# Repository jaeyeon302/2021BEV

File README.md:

# 2021BEV 
2021 Bachelor's degree Graduation Project, Battery Electric Vehicle  
Department of Electrical and Conputer Engineering, Seoul National University  

- Advisor : [Professor Seung-ki Sul](http://eepel.snu.ac.kr/wordpress/professor/)

## Demo Video

### [Test driving 1 : Seoul National University Campus Road (youtube video)](https://youtu.be/YFAJCFfAURw)
- Path length : 4.06Km
- Maximum slope : 7%
- Maximum speed : 30.5km/h

### [Test driving 2 : Cooling Performance test (youtube video)](https://youtu.be/0JFbmtatzrk)
- place : Seoul National University Electric Power Research Institute Parking Lot
- settled down at 44 celcius degree
- continuous maximum q-axis current (30A)

## What I made

### Inverter
- 4 layer PCB artwork (1oz 2oz 2oz 1oz) 
- Used IPM([NFAL5065L4B](https://kr.mouser.com/datasheet/2/308/1/NFAL5065L4B_D-2317681.pdf)) as the power IGBT switch
- Electrically isolated control board area from the High Power Area including IPM and DC link

### DSP - controller
- TMS320F2839D Launchpad
- Built the q-axis current regulator(PI controller with feedforward) from the scratch including resgister setting(ePWM, eCAP, GPIO, Clock, Timer)
- Implemented rotor position and speed observer to estimate right position of rotor for DQ transformation and feedforward control

## Future work
- Robust control algorithm to prevent sudden current peak from the disturbance.   
  Since there is no mechanical damper between ground and motor wheel, Bumpy road surface directly affects the controller's performance
- Hall sensor type curernt sensor removal. because the IPM already provides extra ports to measure the phase current using small register.

## Photos
- [Bicycle Photo](https://photos.app.goo.gl/71CFiTBS6PbSPb559)
- [Inverter Photo](https://photos.app.goo.gl/JQpmmjE8fstSpoiK7)

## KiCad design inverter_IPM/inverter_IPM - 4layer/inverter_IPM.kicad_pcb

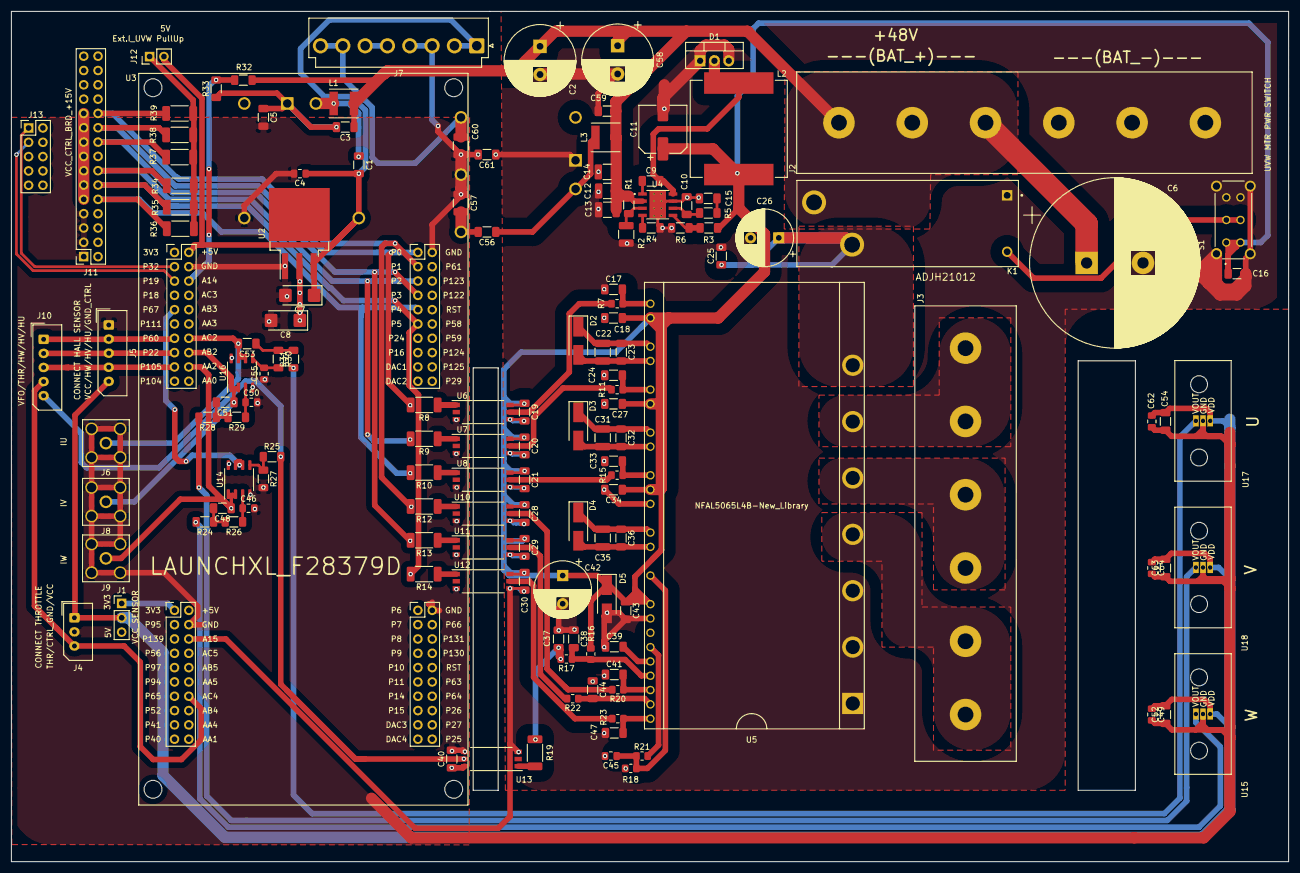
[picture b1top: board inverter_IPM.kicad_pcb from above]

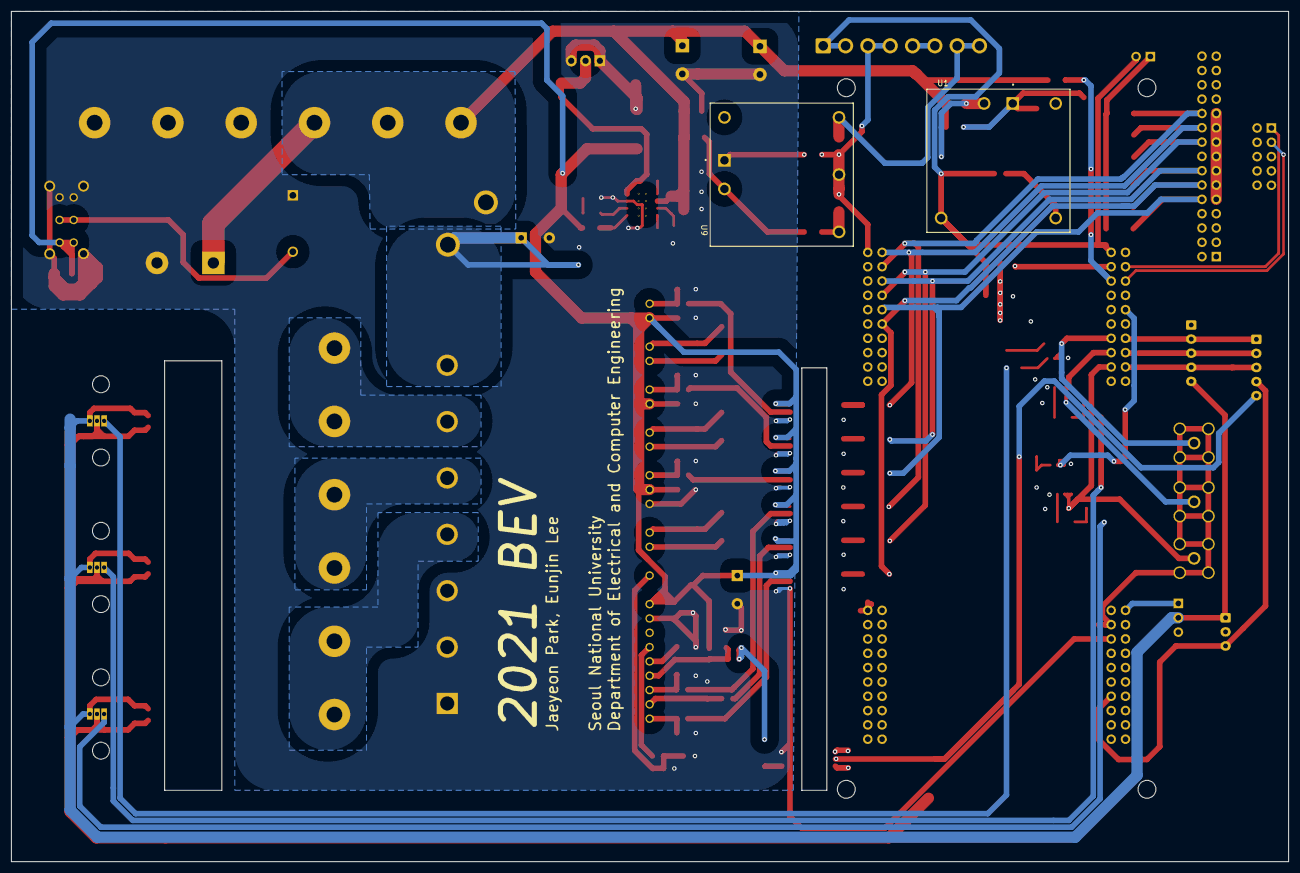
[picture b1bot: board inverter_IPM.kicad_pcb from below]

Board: 4 copper layers, 226.6 x 150.8 mm, 144 parts (2 on the bottom side), 82 nets.

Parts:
C1, C5, C17, C24, C33, C37, C38, C41, C44, C47, C48, C51, C53, C56, C61: 1nF/2KV; C_1206_3216Metric_Pad1.33x1.80mm_HandSolder
C2, C58: 330uF/100V; CP_Radial_D12.5mm_P5.00mm
C3, C59: 1uF; C_1206_3216Metric_Pad1.33x1.80mm_HandSolder
C4, C49, C62, C64: 10uF/25V; C_0805_2012Metric_Pad1.18x1.45mm_HandSolder
C6: 2.2mF; CP_Radial_D30.0mm_P10.00mm_SnapIn
C7, C8: 100uF/16V; CP_EIA-6032-20_AVX-F_Pad2.25x2.35mm_HandSolder
C9, C16, C18, C19, C20, C21, C23, C25, C27, C28, C29, C30, C32, C34, C36, C40, C43, C52, C54, C63: 100nF; C_1206_3216Metric_Pad1.33x1.80mm_HandSolder
C10: 8.2pF; C_1206_3216Metric_Pad1.33x1.80mm_HandSolder
C11: 47uF; CP_Elec_8x11.9
C12, C13, C14: 2.2uF; C_1210_3225Metric_Pad1.33x2.70mm_HandSolder
C15: 750pF; C_1206_3216Metric_Pad1.33x1.80mm_HandSolder
C22, C31, C35, C57, C60: 10uF/100V; C_1210_3225Metric_Pad1.33x2.70mm_HandSolder
C26, C42: 100uF/100V; CP_Radial_D10.0mm_P5.00mm
C39: 1nF/2kV; C_1206_3216Metric_Pad1.33x1.80mm_HandSolder
C45: 10nF; C_0805_2012Metric_Pad1.18x1.45mm_HandSolder
C46, C50, C55: 2.2pF; C_0805_2012Metric_Pad1.18x1.45mm_HandSolder
D1: VFT2080S-E3/4W; TO-220-3_Vertical
D2, D3, D4, D5: SMAZ22-TP; D_SMA_Handsoldering
J1: PinHeader01x03; PinHeader_1x03_P2.54mm_Vertical
J2, J3: BR-1300C-6P
J4: MOLEX01x03; Molex_SPOX_5267-03A_1x03_P2.50mm_Vertical
J5: MOLEX01x05; Molex_SPOX_5267-05A_1x05_P2.50mm_Vertical
J6, J8, J9: SMA; SMA_Amphenol_132203-12_Horizontal
J7: JST8P; JST_VH_B8P-VH-B_1x08_P3.96mm_Vertical
J10: MOLEX_01X05; Molex_SPOX_5267-05A_1x05_P2.50mm_Vertical
J11: Hirose_HIF3BA_30PA_2.54DSA; PinSocket_2x15_P2.54mm_Vertical
J12: PinHeader01x02; PinHeader_1x02_P2.54mm_Vertical
J13: HIF3 2X5; PinHeader_2x05_P2.54mm_Vertical
K1: ADJH21012; Panasonic-ADJH21012-MFG
L1, L3: 4.7uH; L_Taiyo-Yuden_NR-50xx
L2: 15uH, Irms>5A; L_Vishay_IHLP-6767
R1: 442k; R_1206_3216Metric_Pad1.30x1.75mm_HandSolder
R2: 90.9k; R_1210_3225Metric_Pad1.30x2.65mm_HandSolder
R3: 215k; R_1206_3216Metric_Pad1.30x1.75mm_HandSolder
R4: 205k; R_1206_3216Metric_Pad1.30x1.75mm_HandSolder
R5: 44.2k; R_1206_3216Metric_Pad1.30x1.75mm_HandSolder
R6: 12.1k; R_1206_3216Metric_Pad1.30x1.75mm_HandSolder
R7, R11, R15, R17, R20, R22, R23: 100; R_0805_2012Metric_Pad1.20x1.40mm_HandSolder
R8, R9, R10, R12, R13, R14, R19, R34, R35, R36, R37, R38, R39: 1k; R_2010_5025Metric_Pad1.40x2.65mm_HandSolder
R16: 5k; R_0805_2012Metric_Pad1.20x1.40mm_HandSolder
R18: 24; R_0805_2012Metric_Pad1.20x1.40mm_HandSolder
R21: 249; R_0805_2012Metric_Pad1.20x1.40mm_HandSolder
R24, R27, R28, R31: 24k; R_1206_3216Metric_Pad1.30x1.75mm_HandSolder
R25, R26, R29, R30: 12k; R_1206_3216Metric_Pad1.30x1.75mm_HandSolder
R32: 1M; R_1206_3216Metric_Pad1.30x1.75mm_HandSolder
R33: 68k; R_1206_3216Metric_Pad1.30x1.75mm_HandSolder
S1: EG2219; SW_EG2219
U1: PDQE10-Q48-S5-D; CONV_PDQE10-Q48-S5-D
U2: SPX1587AT-3.3; TO-263-3_TabPin4
U3: LAUNCHXL_F28379D
U4: TPS54560BDDA; NOPB
U5: NFAL5065L4B-New_Library; NFAL5065L4B
U6, U7, U8, U10, U11, U12, U13: TLP2748; SO-6L_10x3.84mm_P1.27mm
U9: PDQE10-Q48-D15-D; CONV_PDQE10-Q48-D15-D
U14, U16: LM358; SO-8_3.9x4.9mm_P1.27mm
U15, U17, U18: wcs1800; wcs1x00-xxxx

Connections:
+3V3: C8.1, J1.1, U2.2, U3.1, U3.21
+5V: C1.2, C4.1, C7.1, C40.1, J1.3, J7.1, J7.2, J12.2, U1.3, U2.3, U3.11, U3.31, U13.6
+15V: C11.1, C16.1, C18.1, C19.1, C20.1, C21.1, C27.1, C28.1, C29.1, C30.1, C34.1, C42.1, C43.1, D5.1, L2.2, R3.2, R16.1, S1.1, S1.4, U5.9, U5.13, U5.17, U5.22, U6.6, U7.6, U8.6, U10.6, U11.6, U12.6
/!CTRL_UH: J11.20, R8.2, R38.1, U3.51
/!CTRL_UL: J11.22, R12.2, R39.1, U3.52
/!CTRL_VH: J11.14, R9.2, R34.2, U3.53
/!CTRL_VL: J11.18, R13.2, R37.1, U3.54
/!CTRL_WH: J11.10, R10.2, R36.2, U3.55
/!CTRL_WL: J11.12, R14.2, R35.2, U3.56
/BAT_ADC_DIFF1: R32.2, R33.2, U3.13
/CTRL_UVW_PULLUP: J12.1, R34.1, R35.1, R36.1, R37.2, R38.2, R39.2
/HU: J5.2, J10.1, U3.7
/HV: J5.3, J10.2, U3.8
/HW: J5.4, J10.3, U3.9
/SCIB_RX: J13.1, U3.2
/SCIB_TX: J13.3, U3.3
/THROTTLE: J4.3, J10.4, U3.37
/VCC_CTRL_BRD_+15V: C56.2, C57.2, J7.5, J7.6, J11.9, J11.11, J11.13, J11.15, J11.17, J11.19, J11.21, U9.3, U14.8, U16.8
/VCC_CTRL_BRD_-15V: C60.1, J7.7, J7.8, U9.5
/VCC_SENSOR: C49.1, C52.2, C54.2, C62.1, C63.2, C64.1, J1.2, J4.1, J5.5, U15.1, U17.1, U18.1
/VFO: C37.2, R17.2, R19.2
FB: R3.1, R6.2, U4.5
GND: C2.2, C3.2, C5.1, C6.2, C10.2, C11.2, C12.2, C13.2, C14.2, C15.2, C16.2, C17.1, C18.2, C19.2, C20.2, C21.2, C24.1, C25.2, C26.2, C27.2, C28.2, C29.2, C30.2, C33.1, C34.2, C37.1, C38.1, C39.1, C41.1, C42.2, C43.2, C44.1, C45.2, C47.1, C58.2, C59.2, C61.1, D1.1, D1.3, D5.2, J2.4, J2.5, J2.6, K1.1, R2.2, R4.1, R6.1, R18.1, R33.1, S1.3, S1.6, S1.S1, S1.S2, S1.S3, S1.S4, U1.1, U3.33, U4.7, U4.9, U5.1, U5.2, U5.3, U5.18, U5.23, U6.4, U7.4, U8.4, U9.1, U10.4, U11.4, U12.4, U13.3
GND1: C4.2, C5.2, C7.2, C8.2, C40.2, C46.2, C49.2, C50.2, C52.1, C54.1, C55.1, C57.1, C60.2, C61.2, C62.2, C63.1, C64.2, J4.2, J5.1, J6.2, J7.3, J7.4, J8.2, J9.2, J11.1, J11.3, J11.5, J11.7, R27.2, U1.5, U2.1, U3.12, U3.32, U3.41, U3.61, U6.3, U7.3, U8.3, U9.4, U10.3, U11.3, U12.3, U13.4, U14.4, U15.2, U16.4, U17.2, U18.2
IU: C53.2, J6.1, U3.17, U16.6, U16.7
IV: C51.1, J8.1, U3.18, U16.1, U16.2
IW: C48.1, J9.1, U3.19, U14.1, U14.2
unnamed: C1.1, L1.2, U1.2
unnamed: C9.1, U4.1
unnamed: C10.1, R5.2, U4.6
unnamed: C15.1, R5.1
unnamed: C17.2, R7.1, U5.8
unnamed: C22.1, C23.2, D2.2, U5.11
unnamed: C22.2, C23.1, D2.1, U5.10
unnamed: C24.2, R11.1, U5.12
unnamed: C25.1, C26.1, K1.3, U5.7
unnamed: C31.1, C32.2, D3.2, U5.15
unnamed: C31.2, C32.1, D3.1, U5.14
unnamed: C33.2, R15.1, U5.16
unnamed: C35.1, C36.2, D4.2, U5.20
unnamed: C35.2, C36.1, D4.1, U5.19
unnamed: C38.2, R16.2, R17.1, U5.27
unnamed: C39.2, U5.26
unnamed: C41.2, R20.1, U5.28
unnamed: C44.2, R22.1, U5.29
unnamed: C45.1, R18.2, R21.1, U5.21
unnamed: C46.1, R26.1, U14.3
unnamed: C47.2, R23.1, U5.30
unnamed: C48.2, R24.1, R26.2
unnamed: C50.1, R29.1, U16.3
unnamed: C51.2, R28.1, R29.2
unnamed: C53.1, R30.1, R31.2
unnamed: C55.2, R30.2, U16.5
unnamed: C56.1, L3.2, U9.2
unnamed: K1.2, S1.2, S1.5
unnamed: R1.1, R2.1, U4.3
unnamed: R4.2, U4.4
unnamed: R8.1, U6.1
unnamed: R9.1, U7.1
unnamed: R10.1, U8.1
unnamed: R12.1, U10.1
unnamed: R13.1, U11.1
unnamed: R14.1, U12.1
unnamed: R19.1, U13.1
unnamed: R21.2, U5.25
unnamed: R24.2, U15.3
unnamed: R25.1, R27.1, U14.5
unnamed: R28.2, U18.3
unnamed: R31.1, U17.3
SW_BUCK: C9.2, D1.2, L2.1, U4.8
U: J3.1, J3.2, U5.6
UH: R7.2, U6.5
UL: R20.2, U10.5
V: J3.3, J3.4, U5.5
VDC: C2.1, C3.1, C6.1, C12.1, C13.1, C14.1, C58.1, C59.1, J2.1, J2.2, J2.3, K1.4, L1.1, L3.1, R1.2, R32.1, U4.2
VFO_3V: U3.5, U14.6, U14.7
VFO_5V: J10.5, R25.2, U13.5
VH: R11.2, U7.5
VL: R22.2, U11.5
W: J3.5, J3.6, U5.4
WH: R15.2, U8.5
WL: R23.2, U12.5

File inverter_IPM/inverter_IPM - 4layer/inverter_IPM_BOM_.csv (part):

Source:,G:\???ë¼?´ë¸\0. parkjani2 DRIVE\ì°¸ì¬ PROJECT\?ë¡?í¸\2021 ì¡¸í\2021_ì¡¸í_workspace(shared)\PCB - inverter\inverter_IPM\inverter_IPM - 4layer\inverter_IPM.sch,,,,,,
Date:,2021-03-22 ?¤ì  11:46:58,,,,,,
Tool:,Eeschema (5.1.8)-1,,,,,,
Generator:,C:\Program Files\KiCad\bin\scripting\plugins/bom_csv_grouped_by_value_with_fp.py,,,,,,
Component Count:,144,,,,,,
Ref,Qnty,Value,Cmp name,man#,Footprint,Description,Vendor
"C1, C5, C17, C24, C33, C37, C38, C41, C44, C47, C48, C51, C53, C56, C61, ",15,1nF/2KV,C_Small,C1206C102KGRACTU,Capacitor_SMD:C_1206_3216Metric_Pad1.33x1.80mm_HandSolder,"Unpolarized capacitor, small symbol",
"C2, C58, ",2,330uF/100V,CP1_Small,UVR2A331MHD,Capacitor_THT:CP_Radial_D12.5mm_P5.00mm,"Polarized capacitor, small US symbol",
"C3, C59, ",2,1uF,C_Small,C3216X7R2A105K160AA,Capacitor_SMD:C_1206_3216Metric_Pad1.33x1.80mm_HandSolder,"Unpolarized capacitor, small symbol",
"C4, C49, C62, C64, ",4,10uF/25V,C_Small,TMK212BC6106KG-T,Capacitor_SMD:C_0805_2012Metric_Pad1.18x1.45mm_HandSolder,"Unpolarized capacitor, small symbol",
"C6, ",1,2.2mF,CP1,SLPX222M100E3P3,Capacitor_THT:CP_Radial_D30.0mm_P10.00mm_SnapIn,"Polarized capacitor, US symbol",
"C7, C8, ",2,100uF/16V,CP1_Small,F931C107MCC,Capacitor_Tantalum_SMD:CP_EIA-6032-20_AVX-F_Pad2.25x2.35mm_HandSolder,"Polarized capacitor, small US symbol",
"C9, C16, C18, C19, C20, C21, C23, C25, C27, C28, C29, C30, C32, C34, C36, C40, C43, C52, C54, C63, ",20,100nF,C_Small,HMF316B7104KLHT,Capacitor_SMD:C_1206_3216Metric_Pad1.33x1.80mm_HandSolder,"Unpolarized capacitor, small symbol",
"C10, ",1,8.2pF,C_Small,C1206C829D5GACTU,Capacitor_SMD:C_1206_3216Metric_Pad1.33x1.80mm_HandSolder,"Unpolarized capacitor, small symbol",
"C11, ",1,47uF,CP1_Small,A768KS476M1JLAE031,Capacitor_SMD:CP_Elec_8x11.9,"Polarized capacitor, small US symbol",
"C12, C13, C14, ",3,2.2uF,C_Small,HMK325BJ225KM-P,Capacitor_SMD:C_1210_3225Metric_Pad1.33x2.70mm_HandSolder,"Unpolarized capacitor, small symbol",
"C15, ",1,750pF,C_Small,C1206C751J5GACTU,Capacitor_SMD:C_1206_3216Metric_Pad1.33x1.80mm_HandSolder,"Unpolarized capacitor, small symbol",
"C22, C31, C35, C57, C60, ",5,10uF/100V,C_Small,GRM32EC72A106KE05L,Capacitor_SMD:C_1210_3225Metric_Pad1.33x2.70mm_HandSolder,"Unpolarized capacitor, small symbol",
"C26, C42, ",2,100uF/100V,CP1_Small,EEU-FR2A101,Capacitor_THT:CP_Radial_D10.0mm_P5.00mm,"Polarized capacitor, small US symbol",
"C39, ",1,1nF/2kV,C_Small,C1206C102KGRACTU,Capacitor_SMD:C_1206_3216Metric_Pad1.33x1.80mm_HandSolder,"Unpolarized capacitor, small symbol",
"C45, ",1,10nF,C_Small,GRM2195C1H103JA01D,Capacitor_SMD:C_0805_2012Metric_Pad1.18x1.45mm_HandSolder,"Unpolarized capacitor, small symbol",
"C46, C50, C55, ",3,2.2pF,C_Small,VJ0805A2R2BXACW1BC,Capacitor_SMD:C_0805_2012Metric_Pad1.18x1.45mm_HandSolder,"Unpolarized capacitor, small symbol",
"D1, ",1,VFT2080S-E3/4W,D_Schottky_AKA,VFT2080S-E3/4W,Package_TO_SOT_THT:TO-220-3_Vertical,"Schottky diode, anode on pins 1 and 3",
"D2, D3, D4, D5, ",4,SMAZ22-TP,D_Zener_Small,SMAZ22-TP,Diode_SMD:D_SMA_Handsoldering,"Zener diode, small symbol",
"J1, ",1,PinHeader01x03,Conn_01x03,PinHeader01x03,Connector_PinHeader_2.54mm:PinHeader_1x03_P2.54mm_Vertical,"Generic connector, single row, 01x03, script generated (kicad-library-utils/schlib/autogen/connector/)",
"J2, J3, ",2,BR-1300C-6P,Conn_01x06,BR-1300C-6P,j_terminal:BR-1300C-6P,"Generic connector, single row, 01x06, script generated (kicad-library-utils/schlib/autogen/connector/)",
"J4, ",1,MOLEX01x03,Conn_01x03,MOLEX_5267-03,Connector_Molex:Molex_SPOX_5267-03A_1x03_P2.50mm_Vertical,"Generic connector, single row, 01x03, script generated (kicad-library-utils/schlib/autogen/connector/)",
"J5, ",1,MOLEX01x05,Conn_01x05,MOLEX_5267-05,Connector_Molex:Molex_SPOX_5267-05A_1x05_P2.50mm_Vertical,"Generic connector, single row, 01x05, script generated (kicad-library-utils/schlib/autogen/connector/)",
"J6, J8, J9, ",3,SMA,Conn_Coaxial,SMA,Connector_Coaxial:SMA_Amphenol_132203-12_Horizontal,"coaxial connector (BNC, SMA, SMB, SMC, Cinch/RCA, ...)",
"J7, ",1,JST8P,Conn_01x08,JST8P,Connector_JST:JST_VH_B8P-VH-B_1x08_P3.96mm_Vertical,"Generic connector, single row, 01x08, script generated (kicad-library-utils/schlib/autogen/connector/)",
"J10, ",1,MOLEX_01X05,Conn_01x05,molex-01x05,Connector_Molex:Molex_SPOX_5267-05A_1x05_P2.50mm_Vertical,"Generic connector, single row, 01x05, script generated (kicad-library-utils/schlib/autogen/connector/)",
"J11, ",1,Hirose_HIF3BA_30PA_2.54DSA,Conn_02x15_Odd_Even,,Connector_PinSocket_2.54mm:PinSocket_2x15_P2.54mm_Vertical,"Generic connector, double row, 02x15, odd/even pin numbering scheme (row 1 odd numbers, row 2 even numbers), script generated (kicad-library-utils/schlib/autogen/connector/)",
"J12, ",1,PinHeader01x02,Conn_01x02,pinheader 01x02,Connector_PinHeader_2.54mm:PinHeader_1x02_P2.54mm_Vertical,"Generic connector, single row, 01x02, script generated (kicad-library-utils/schlib/autogen/connector/)",
"J13, ",1,HIF3 2X5,Conn_02x05_Odd_Even,HIF3 2X5,Connector_PinHeader_2.54mm:PinHeader_2x05_P2.54mm_Vertical,"Generic connector, double row, 02x05, odd/even pin numbering scheme (row 1 odd numbers, row 2 even numbers), script generated (kicad-library-utils/schlib/autogen/connector/)",
"K1, ",1,ADJH21012,ADJH21012,ADJH21012,j_power_switch:Panasonic-ADJH21012-MFG,ADJH21012,
"L1, L3, ",2,4.7uH,L_Small,NRS5024T4R7MMGJV,Inductor_SMD:L_Taiyo-Yuden_NR-50xx,"Inductor, small symbol",
"L2, ",1,"15uH, Irms>5A",L,IHLP6767GZER150M01,Inductor_SMD:L_Vishay_IHLP-6767,Inductor,
"R1, ",1,442k,R_Small,HV732BTTD4423F,Resistor_SMD:R_1206_3216Metric_Pad1.30x1.75mm_HandSolder,"Resistor, small symbol",
"R2, ",1,90.9k,R_Small,CRCW121090K9FKEA,Resistor_SMD:R_1210_3225Metric_Pad1.30x2.65mm_HandSolder,"Resistor, small symbol",
"R3, ",1,215k,R_Small,CRCW1206215KFKEA,Resistor_SMD:R_1206_3216Metric_Pad1.30x1.75mm_HandSolder,"Resistor, small symbol",
"R4, ",1,205k,R_Small,CRCW1206205KFKEA,Resistor_SMD:R_1206_3216Metric_Pad1.30x1.75mm_HandSolder,"Resistor, small symbol",
"R5, ",1,44.2k,R_Small,ERA-8AEB4422V,Resistor_SMD:R_1206_3216Metric_Pad1.30x1.75mm_HandSolder,"Resistor, small symbol",
"R6, ",1,12.1k,R_Small,ERA-8AEB1212V,Resistor_SMD:R_1206_3216Metric_Pad1.30x1.75mm_HandSolder,"Resistor, small symbol",
"R7, R11, R15, R17, R20, R22, R23, ",7,100,R_Small,CHP0805AFX-1000ELF,Resistor_SMD:R_0805_2012Metric_Pad1.20x1.40mm_HandSolder,"Resistor, small symbol",
"R8, R9, R10, R12, R13, R14, R19, R34, R35, R36, R37, R38, R39, ",13,1k,R_Small,CMP2010AFX-1001ELF,Resistor_SMD:R_2010_5025Metric_Pad1.40x2.65mm_HandSolder,"Resistor, small symbol",
"R16, ",1,5k,R_Small,CRCW08055K00FKTA,Resistor_SMD:R_0805_2012Metric_Pad1.20x1.40mm_HandSolder,"Resistor, small symbol",
"R18, ",1,24,R_Small,RK73H2ATTD24R0F,Resistor_SMD:R_0805_2012Metric_Pad1.20x1.40mm_HandSolder,"Resistor, small symbol",
"R21, ",1,249,R_Small,RK73H2ATTD2490F,Resistor_SMD:R_0805_2012Metric_Pad1.20x1.40mm_HandSolder,"Resistor, small symbol",
"R24, R27, R28, R31, ",4,24k,R_Small,CR1206-JW-243ELF,Resistor_SMD:R_1206_3216Metric_Pad1.30x1.75mm_HandSolder,"Resistor, small symbol",
"R25, R26, R29, R30, ",4,12k,R_Small,CRCW120612K0FKEAC,Resistor_SMD:R_1206_3216Metric_Pad1.30x1.75mm_HandSolder,"Resistor, small symbol",
"R32, ",1,1M,R_Small,ERA-8AED105V,Resistor_SMD:R_1206_3216Metric_Pad1.30x1.75mm_HandSolder,"Resistor, small symbol",
"R33, ",1,68k,R_Small,CRCW120668K0FKEAHP,Resistor_SMD:R_1206_3216Metric_Pad1.30x1.75mm_HandSolder,"Resistor, small symbol",
"S1, ",1,EG2219,EG2219,EG2219,j_switch:SW_EG2219,,
"U1, ",1,PDQE10-Q48-S5-D,PDQE10-Q48-S5-D,PDQE10-Q48-S5-D,PDQE10:CONV_PDQE10-Q48-S5-D,,
"U2, ",1,SPX1587AT-3.3,AZ1117-5.0,SPX1587AT-3.3,Package_TO_SOT_SMD:TO-263-3_TabPin4,"1A 20V Fixed LDO Linear Regulator, 5.0V, SOT-89/SOT-223/TO-220/TO-252/TO-263",
"U3, ",1,LAUNCHXL_F28379D,LAUNCHXL_F28379D,LAUNCHPAD_F28379D,j_modules:LAUNCHXL_F28379D,,
"U4, ",1,TPS54560BDDA,TPS54560BDDA,TPS54560BDDA,j_regulator_switching:NOPB,,
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
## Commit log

2021-03-03 hall_sensor_release 0.1
2021-03-03 synchronize ECAP clock counter
2021-03-03 apply real gpio pin for hall sensors
2021-03-03 fix the change in carrier wave from pwm pn & sync the counter in eCAP
2021-03-04 sync hall sensor and ePWM
2021-03-04 fix the varied frequency bug in ePWM
    the carrier frequency of ePWM is varied because of the external sync source or some other sources.
    solution : disable PHSEN bit like this
    ePWM.TBCTL.bit.PHSEN = 0
2021-03-04 add pwm testcode
2021-03-04 add ADC and connect EPWMxSOCA <-> ADC
2021-03-04 ADC complete (throttle and battery)
2021-03-04 ePWMxSOCB triggers throttle ADC conversion
2021-03-04 adc sampilng에 대한 설명 변경
2021-03-05 connect control_function to call after completing ADC Sample&Hold and conversion
2021-03-05 complete basic commutation logic
2021-03-05 add controller sketch
2021-03-08 change unit system to MKS
2021-03-08 build error fixed
2021-03-08 Kp, Ki fixed
    update coefficient for PI controller with Anti windup
    update control motor having trapezoidal back EMF pulse shape
2021-03-09 fix wrong phase flag
2021-03-09 remove ePWM test code
2021-03-09 fix dumb epwm AQCTLB
2021-03-09 fix dumb mistake about PWM
2021-03-09 add comments for TEST-mode
2021-03-09 fix typo
2021-03-11 add deadband
2021-03-11 add comments to hall sensor
2021-03-11 write testcode
2021-03-11 change flash mode
2021-03-11 fix inverted pwm output
2021-03-11 add indicator led
2021-03-11 add control logic
2021-03-12 hall_sensor2 test
2021-03-12 Change hall_sensor and DQ control logic
    not using eCAP
    organize DQ control logic
2021-03-12 organized DQ PI control logic
2021-03-16 add test
2021-03-16 add initila adc sampling to measure offset voltage
2021-03-16 ADD HALL SENSOR ANGLE UPDATE & change throttle ADCIN to 5 from 4
2021-03-18 change ADC channel
2021-03-23 integrate hall sensor
2021-04-02 2121 Epwm OUTOUT POLARITY
2021-04-02 change duty and comment for pwm
2021-04-06 fix offset sampling
2021-04-06 test dq transformation
2021-04-07 fix initial ePWM duty configuration
2021-04-08 save me
    1. epwm sync fixed
    2. right before Vector Current Control
2021-04-08 fix zubbul
    hate disconnected wire
2021-04-08 fix angle_E_rad not updated
2021-04-08 fix integer division problem
2021-04-10 linear interpolation hall sensor
2021-04-12 while adding observer
2021-04-13 initial success!!!
2021-04-15 complete!
2021-04-15 max speed up
2021-04-19 change max iq command current
2021-04-27 change current sensor(wcs1700) that has -70A to 70A current range
2021-04-27 change to max current 35A
2021-04-29 phase W is wrong
2021-04-30 750W motor
2021-06-20 add PCB schematics
2021-08-20 FIX MISINFORMATION ABOUT POWER SWITCH
    NFAL5065L4B is not the mosfet switch, it is IGBT switchi
